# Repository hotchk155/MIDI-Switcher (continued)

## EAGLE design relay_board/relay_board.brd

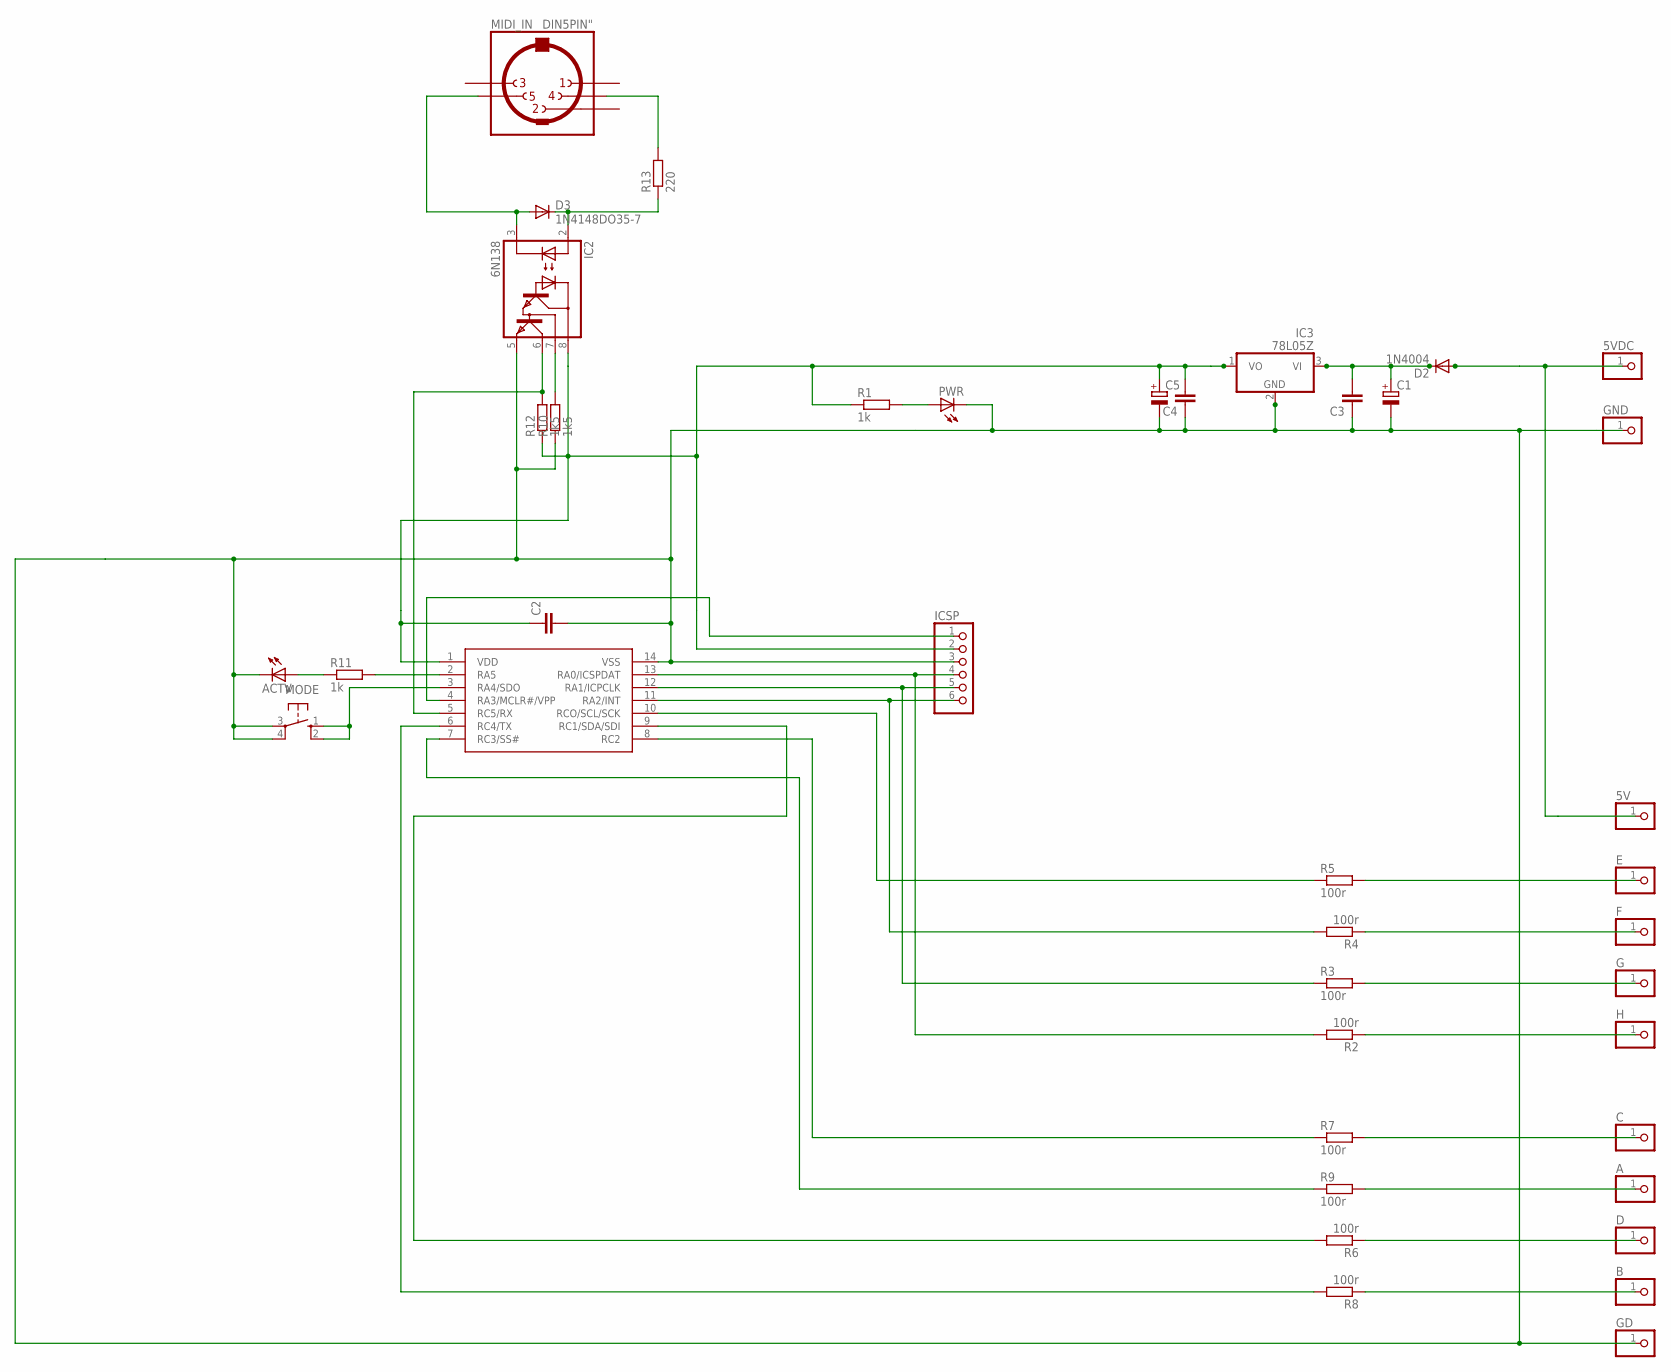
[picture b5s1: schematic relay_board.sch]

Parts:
5V, 5VDC: PINHD-1X1; 1X01
A: PINHD-1X1; 1X01
ACTV: LED3MM
B: PINHD-1X1; 1X01
C: PINHD-1X1; 1X01
C1: CPOL-EUE2.5-7; E2,5-7
C2, C3, C4: C2.5/2; C2.5-2
C5: CPOL-EUE2-5; E2-5
D: PINHD-1X1; 1X01
D2: 1N4004; DO-VERT
D3: 1N4148DO35-7; DO35-7
E: PINHD-1X1; 1X01
F: PINHD-1X1; 1X01
G: PINHD-1X1; 1X01
GD: PINHD-1X1; 1X01
GND: PINHD-1X1; 1X01
H: PINHD-1X1; 1X01
IC1: PIC16F1825DIL14; DIL14
IC2: 6N138; DIL08
IC3: 78L05Z; TO92
ICSP: HEADER-1X6; 1X06_OVAL
MIDI_IN: DIN5PIN"; TRUCONN90
MODE: 10-XX; B3F-10XX
PWR: LED3MM
R1, R11: 1k; 0207/2V
R2, R3, R4, R5, R6, R7, R8, R9: 100r; 0207/2V
R10, R12: 1k5; 0207/2V
R13: 220; 0207/7

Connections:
3V3: C2.1, C4.2, C5.+, IC1.1 (VDD), IC2.8 (VCC), IC3.1 (VO), ICSP.2, R1.1, R12.1
GND: ACTV.K (C), C1.-, C2.2, C3.1, C4.1, C5.-, GD.1, GND.1, IC1.14 (VSS), IC2.5 (GND), IC3.2 (GND), ICSP.3, MODE.3, MODE.4 (P1), PWR.K (C), R10.1
unnamed: 5V.1, 5VDC.1, D2.A
unnamed: PWR.A, R1.2
unnamed: C1.+, C3.2, D2.C, IC3.3 (VI)
unnamed: MIDI_IN.4, R13.2
unnamed: D3.C, IC2.2 (A), R13.1
unnamed: D3.A, IC2.3 (C), MIDI_IN.5
unnamed: IC2.7 (VB), R10.2
unnamed: F.1, R4.1
unnamed: G.1, R3.2
unnamed: H.1, R2.1
unnamed: C.1, R7.2
unnamed: A.1, R9.2
unnamed: D.1, R6.1
unnamed: B.1, R8.1
unnamed: IC1.12 (RA1/ICPCLK), ICSP.5, R3.1
unnamed: IC1.13 (RA0/ICSPDAT), ICSP.4, R2.2
unnamed: IC1.8 (RC2), R7.1
unnamed: IC1.7 (RC3/SS#), R9.1
unnamed: IC1.9 (RC1/SDA/SDI), R6.2
unnamed: IC1.6 (RC4/TX), R8.2
unnamed: E.1, R5.2
unnamed: IC1.4 (RA3/MCLR#/VPP), ICSP.1
unnamed: IC1.3 (RA4/SDO), MODE.1 (S), MODE.2 (S1)
unnamed: IC1.11 (RA2/INT), ICSP.6, R4.2
unnamed: IC1.10 (RCO/SCL/SCK), R5.1
unnamed: IC1.5 (RC5/RX), IC2.6 (VO), R12.2
unnamed: ACTV.A, R11.1
unnamed: IC1.2 (RA5), R11.2

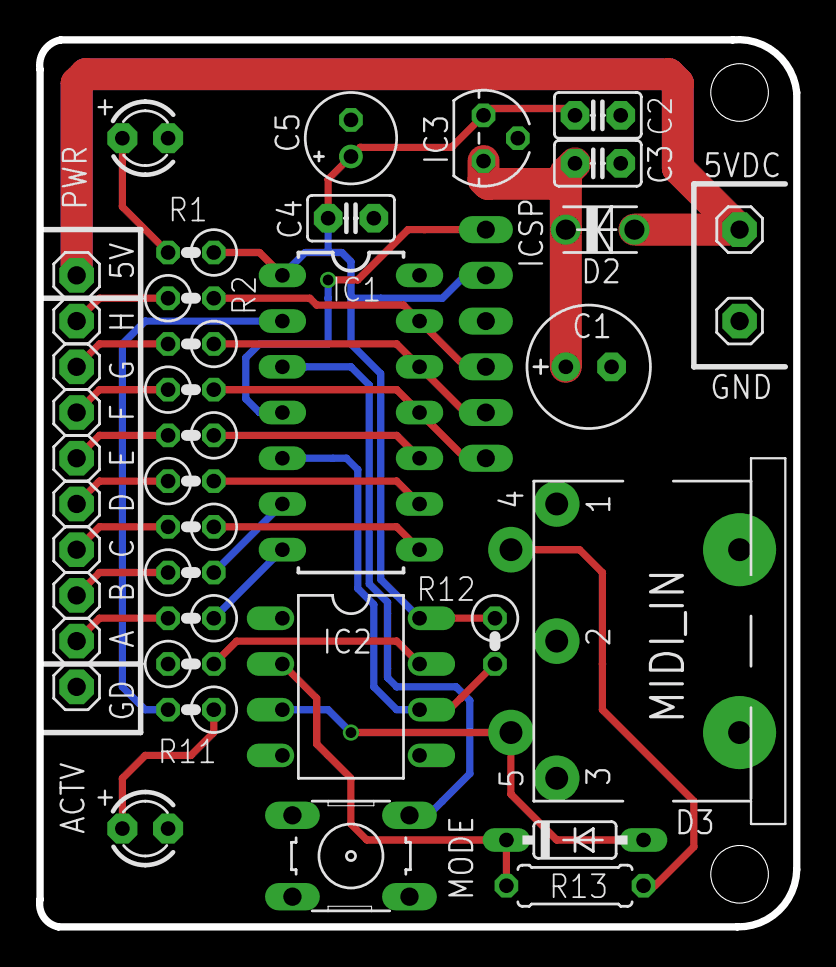
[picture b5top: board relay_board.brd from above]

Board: 2 copper layers, 42.1 x 49.3 mm, 40 parts (0 on the bottom side), 30 nets.

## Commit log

2013-03-10 tweaks
2013-06-02 revisions to pcb
2013-11-13 in progress
2013-11-13 adding config app
2013-11-17 app updates
2013-11-17 starting docs
2013-12-01 changes to silkscreen
2013-12-21 Release v1
2013-12-21 images
2015-01-03 rev4 - tip120
2015-01-03 midi thru pins
2015-01-06 relay board v1
2015-01-06 rev 1
2015-02-06 relay switcher rev2
2015-02-06 midi switcher rev5
2015-03-11 docs updates
2015-03-11 sexed up dossier
2015-03-20 working on relay board
2015-03-21 V1.2 First release of Relay Switcher
2015-03-21 packing slip
2015-08-14 fix eagle consistency error
2015-08-29 SMT board
2015-09-28 version 7
2016-07-17 first version draft
2016-07-18 REV 1 FINAL
2016-11-20 LED PWM
2016-11-25 interrupt approach #2
2016-11-27 using CCP modules to implement 3 fast PWM channels for RGB
2016-12-17 update LED switcher firmware
2016-12-17 rev0.1
2016-12-17 led switcher 0.1 release
2017-07-23 new layout
2017-07-24 tidy
2017-07-24 sockets on mm grid
2017-07-24 done?
2018-01-29 dfsfds
2018-01-30 REED RELAY MODULE REV1
2018-07-10 prep to splt up projects
2018-07-10 moved smt board
2018-07-11 rename
2018-10-02 version 1.03 adds support for new SMT switcher
2018-12-08 adding docs for website
2018-12-08 docs
2020-04-30 packing slip update
